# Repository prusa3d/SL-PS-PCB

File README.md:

# PRUSA Power supply for SL1

KiCad PCB layout

* [Interactive bom](http://htmlpreview.github.io/?https://github.com/prusa3d/SL-PS-PCB/blob/master/rev.1.4.1/ibom.html)
* [STEP 3D model](rev.1.4.1/sl-ps-141.step)

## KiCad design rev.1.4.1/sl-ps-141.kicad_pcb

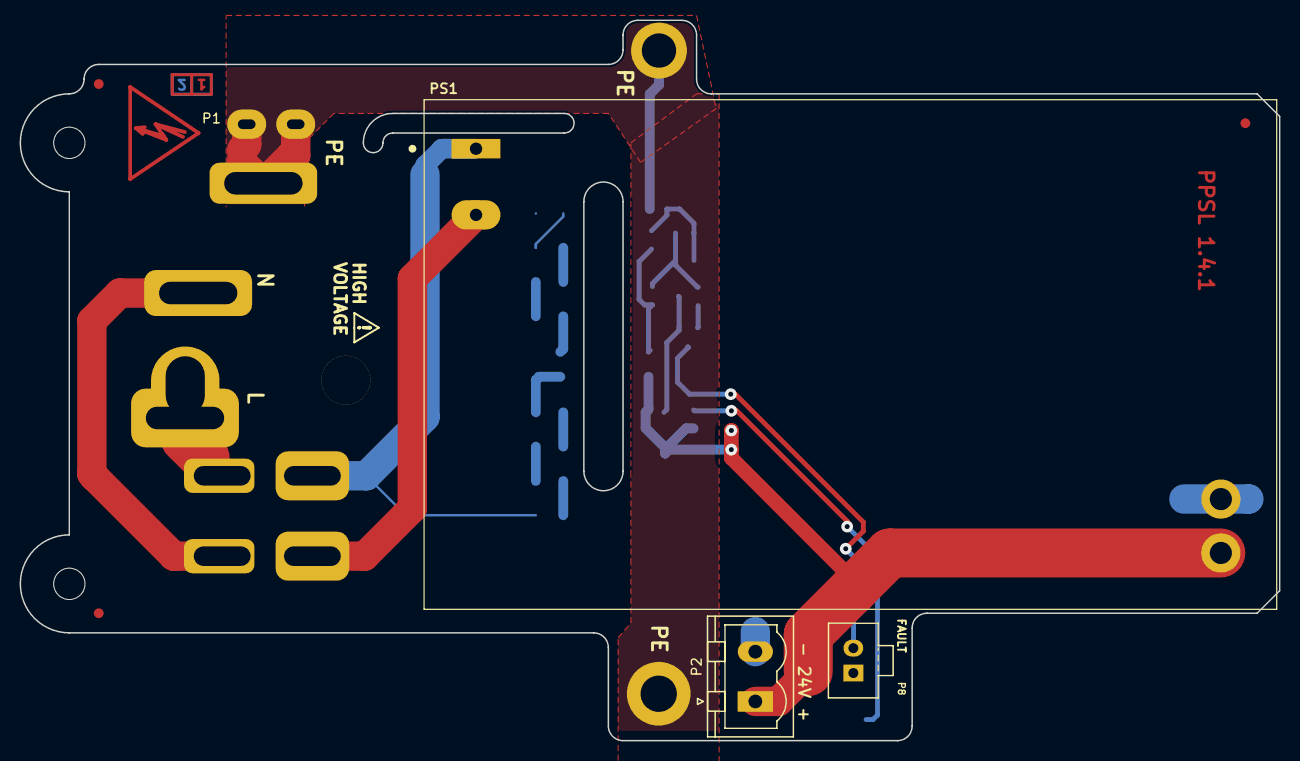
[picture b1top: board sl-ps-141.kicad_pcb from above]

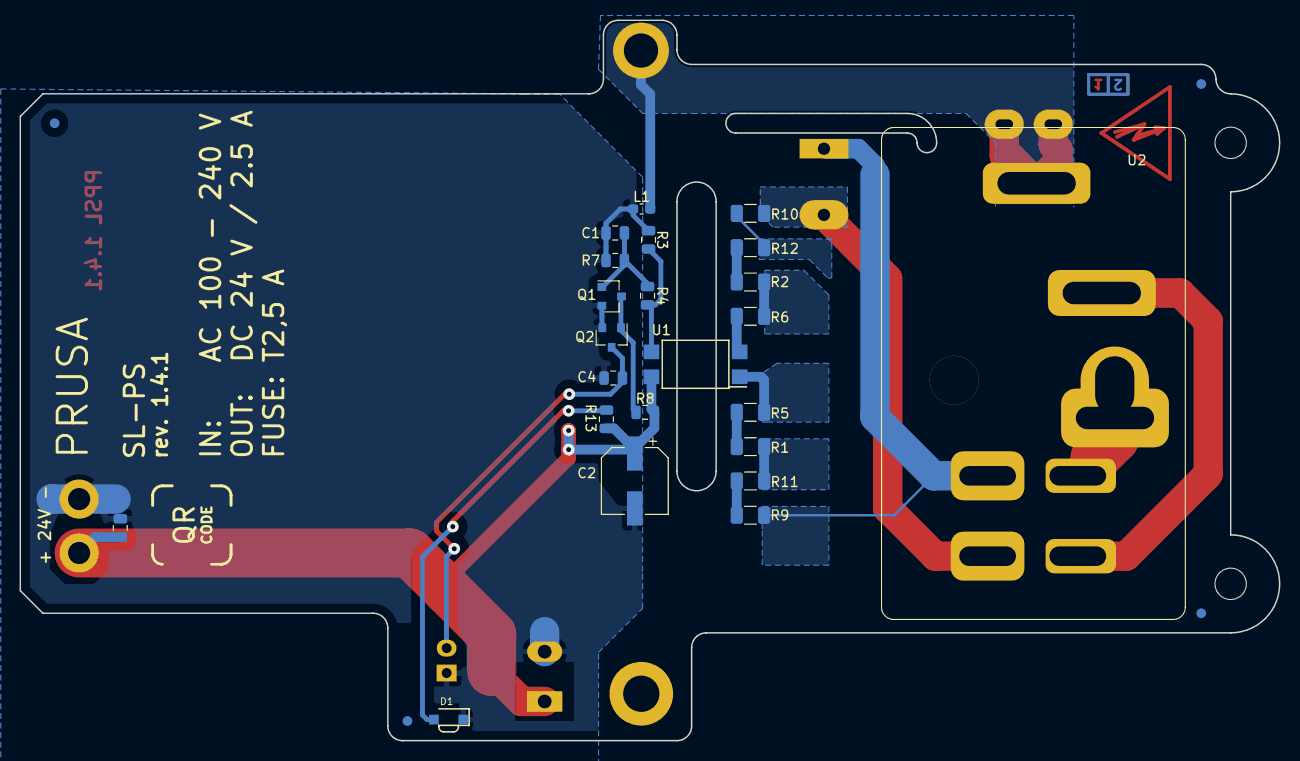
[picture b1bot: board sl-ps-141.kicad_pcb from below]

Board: 2 copper layers, 128.5 x 73.5 mm, 34 parts (24 on the bottom side), 20 nets.

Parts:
C1: 330n; C_0805_2012Metric
C2: 22u; CP_Elec_6.3x5.3
C3: *100n; C_0805_2012Metric
C4: 100n; C_0805_2012Metric
D1: KPA-3010MGC; LED-1104
H1, H2: MountingHole; MountingHole_3.2mm_M3
H3, H4: MountingHole_Pad; MountingHole_3.2mm_M3_ISO14580_Pad
L1: BLM18KG121TN1D; R_0603_1608Metric_Pad1.05x0.95mm_HandSolder
M1: ZKT-2.5A; MEC
M2: *QR_CODE; QR-code-8x8mm
P1: *PE; faston-hole-m
P2: TBG-5-PW-2P/GN; PhoenixContact_MSTBVA-G_02x5.08mm_Vertical
P8: MOLEX 70543-0001; Pin_1x02-XL
PS1: IRM-60-24; CONV_IRM-60-48
Q1, Q2: NTR5103NT1G; SOT-23
R1, R2, R5, R6, R9, R10, R11, R12: 11k; R_1206_3216Metric
R3, R8, R13: 10k; R_0805_2012Metric
R4: 33k; R_0805_2012Metric
R7: 100k; R_0805_2012Metric
SYM1: *SYM_Flash_Small; Symbol_HighVoltage_Type2_CopperTop_VerySmall
U1: ISP814XSM; Optocoupler_SMD_LTV-817S
U2: AC_connector_IEC60320_sw_fus; ps_con_sw_acd

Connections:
/+24V: C2.1, C3.1, P2.1, PS1.+V, R8.2, R13.2, U1.4
/AC_L: PS1.AC/L, R9.1, U2.5
/AC_N: PS1.AC/N, R10.1, U2.7
/L: U2.1, U2.4
/L1: R9.2, R11.1
/L2: R1.1, R11.2
/L3: R1.2, R5.1
/L4: R5.2, U1.1
/N: U2.2, U2.6
/N1: R10.2, R12.1
/N2: R2.1, R12.2
/N3: R2.2, R6.1
/N4: R6.2, U1.2
/PE: H3.1, H4.1, L1.2, P1.1, U2.3
/RC: C1.1, Q1.1, R4.1, R7.1
GND: C1.2, C2.2, C3.2, C4.2, D1.1, L1.1, P2.2, P8.1, PS1.V, Q1.2, Q2.2, R3.2, R7.2
unnamed: C4.1, P8.2, Q2.3
unnamed: D1.2, R13.1
unnamed: Q1.3, Q2.1, R8.1
unnamed: R3.1, R4.2, U1.3

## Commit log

2019-09-20 directory structure
2019-09-20 name update
